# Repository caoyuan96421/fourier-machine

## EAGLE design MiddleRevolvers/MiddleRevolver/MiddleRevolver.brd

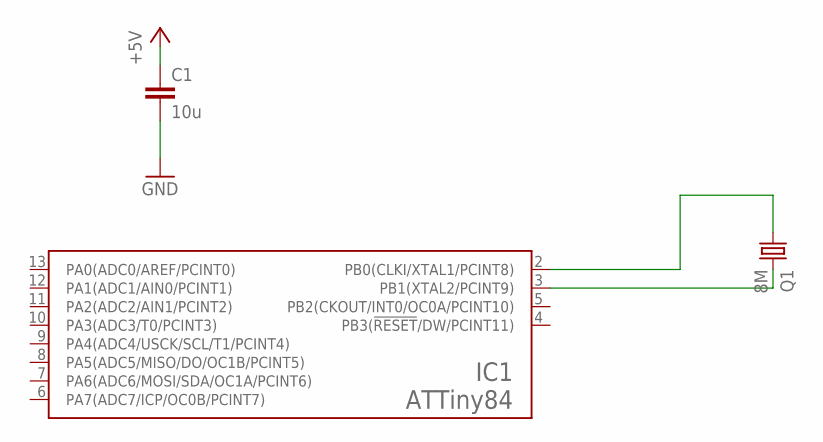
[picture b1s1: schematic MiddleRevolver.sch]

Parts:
C1: 10u; C0805
IC1: ATTiny84; DIL14
Q1: 8M; HC49/S

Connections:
+5V: C1.1
GND: C1.2, IC1.14 (GND)
unnamed: IC1.2 (PB0(CLKI/XTAL1/PCINT8)), Q1.1
unnamed: IC1.3 (PB1(XTAL2/PCINT9)), Q1.2
UCC: IC1.1 (UCC)

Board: 2 copper layers, 3 parts (0 on the bottom side), 3 nets, no tracks yet.

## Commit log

2015-03-17 :tada: Added .gitattributes & .gitignore files
2015-03-17 stepper-test
2015-05-03 Software-Java
2015-05-03 Updated Top Revolver circuit
2015-06-23 test and backup
